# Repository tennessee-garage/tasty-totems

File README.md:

# tasty-totems
Repo for a zoetrope type of art project

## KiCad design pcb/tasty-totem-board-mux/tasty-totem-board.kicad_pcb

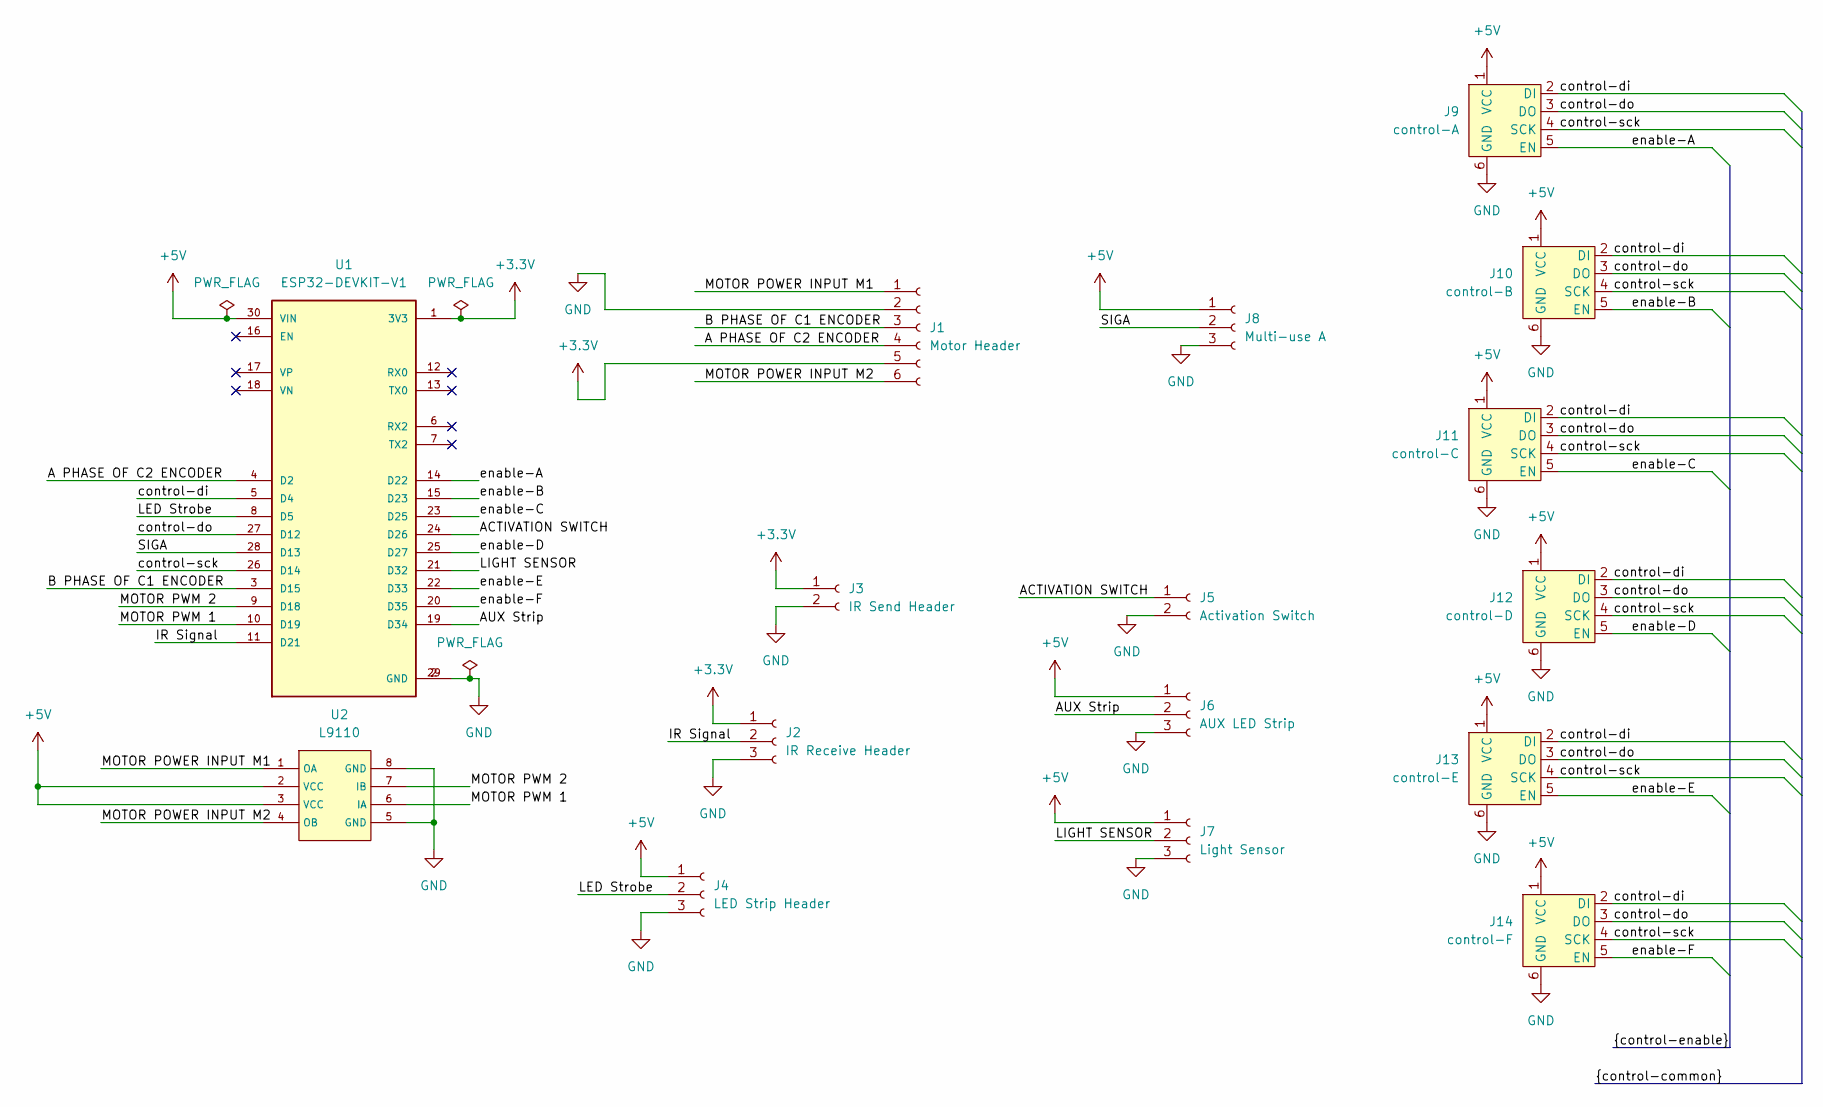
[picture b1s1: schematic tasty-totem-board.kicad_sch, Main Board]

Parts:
J1: Motor Header; PinSocket_1x06_P2.54mm_Horizontal
J2: IR Receive Header; PinSocket_1x03_P2.54mm_Horizontal
J3: IR Send Header; PinSocket_1x02_P2.54mm_Horizontal
J4: LED Strip Header; PinSocket_1x03_P2.54mm_Horizontal
J5: Activation Switch; PinSocket_1x02_P2.54mm_Horizontal
J6: AUX LED Strip; PinSocket_1x03_P2.54mm_Horizontal
J7: Light Sensor; PinSocket_1x03_P2.54mm_Horizontal
J8: Multi-use A; PinSocket_1x03_P2.54mm_Horizontal
J9: control-A; RJ11-RA
J10: control-B; RJ11-RA
J11: control-C; RJ11-RA
J12: control-D; RJ11-RA
J13: control-E; RJ11-RA
J14: control-F; RJ11-RA
U1: ESP32-DEVKIT-V1; MODULE_ESP32_DEVKIT_V1; PARTREV N/A
U2: L9110; DIP-8_W7.62mm

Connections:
+3.3V: J1.5, J2.1, J3.1, U1.1 (3V3)
+5V: J4.1, J6.1, J7.1, J8.1, J9.1 (VCC), J10.1 (VCC), J11.1 (VCC), J12.1 (VCC), J13.1 (VCC), J14.1 (VCC), U1.30 (VIN), U2.2 (VCC), U2.3 (VCC)
/A PHASE OF C2 ENCODER: J1.4, U1.4 (D2)
/ACTIVATION SWITCH: J5.1, U1.24 (D26)
/AUX Strip: J6.2, U1.19 (D34)
/B PHASE OF C1 ENCODER: J1.3, U1.3 (D15)
/IR Signal: J2.2, U1.11 (D21)
/LED Strobe: J4.2, U1.8 (D5)
/LIGHT SENSOR: J7.2, U1.21 (D32)
/MOTOR POWER INPUT M1: J1.1, U2.1 (OA)
/MOTOR POWER INPUT M2: J1.6, U2.4 (OB)
/MOTOR PWM 1: U1.10 (D19), U2.6 (IA)
/MOTOR PWM 2: U1.9 (D18), U2.7 (IB)
/SIGA: J8.2, U1.28 (D13)
/control-di: J9.2 (DI), J10.2 (DI), J11.2 (DI), J12.2 (DI), J13.2 (DI), J14.2 (DI), U1.5 (D4)
/control-do: J9.3 (DO), J10.3 (DO), J11.3 (DO), J12.3 (DO), J13.3 (DO), J14.3 (DO), U1.27 (D12)
/control-sck: J9.4 (SCK), J10.4 (SCK), J11.4 (SCK), J12.4 (SCK), J13.4 (SCK), J14.4 (SCK), U1.26 (D14)
/enable-A: J9.5 (EN), U1.14 (D22)
/enable-B: J10.5 (EN), U1.15 (D23)
/enable-C: J11.5 (EN), U1.23 (D25)
/enable-D: J12.5 (EN), U1.25 (D27)
/enable-E: J13.5 (EN), U1.22 (D33)
/enable-F: J14.5 (EN), U1.20 (D35)
GND: J1.2, J2.3, J3.2, J4.3, J5.2, J6.3, J7.3, J8.3, J9.6 (GND), J10.6 (GND), J11.6 (GND), J12.6 (GND), J13.6 (GND), J14.6 (GND), U1.2 (GND), U1.29 (GND), U2.5 (GND), U2.8 (GND)

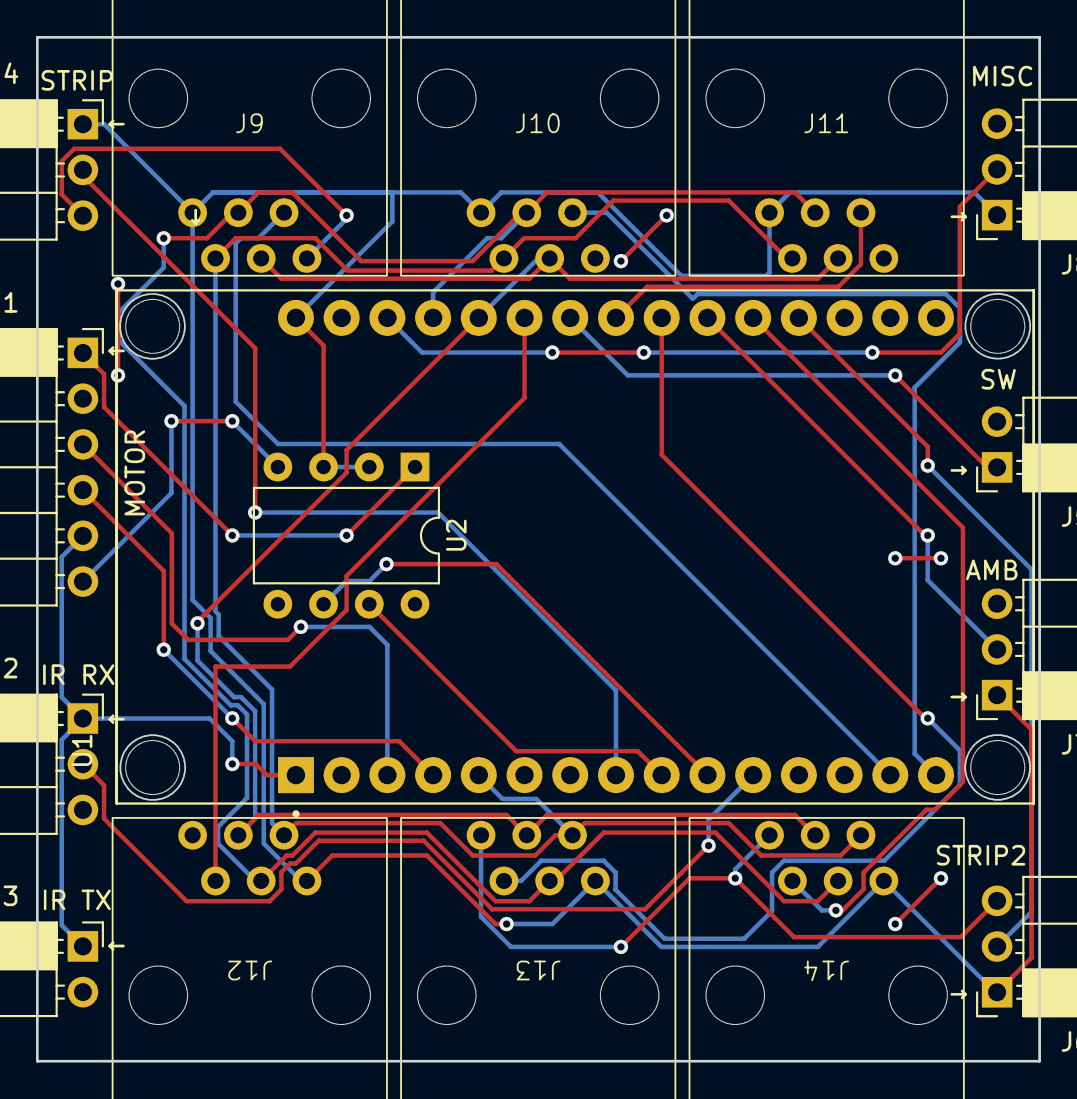
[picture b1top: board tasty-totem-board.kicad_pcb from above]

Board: 2 copper layers, 55.7 x 56.9 mm, 16 parts (0 on the bottom side), 24 nets.

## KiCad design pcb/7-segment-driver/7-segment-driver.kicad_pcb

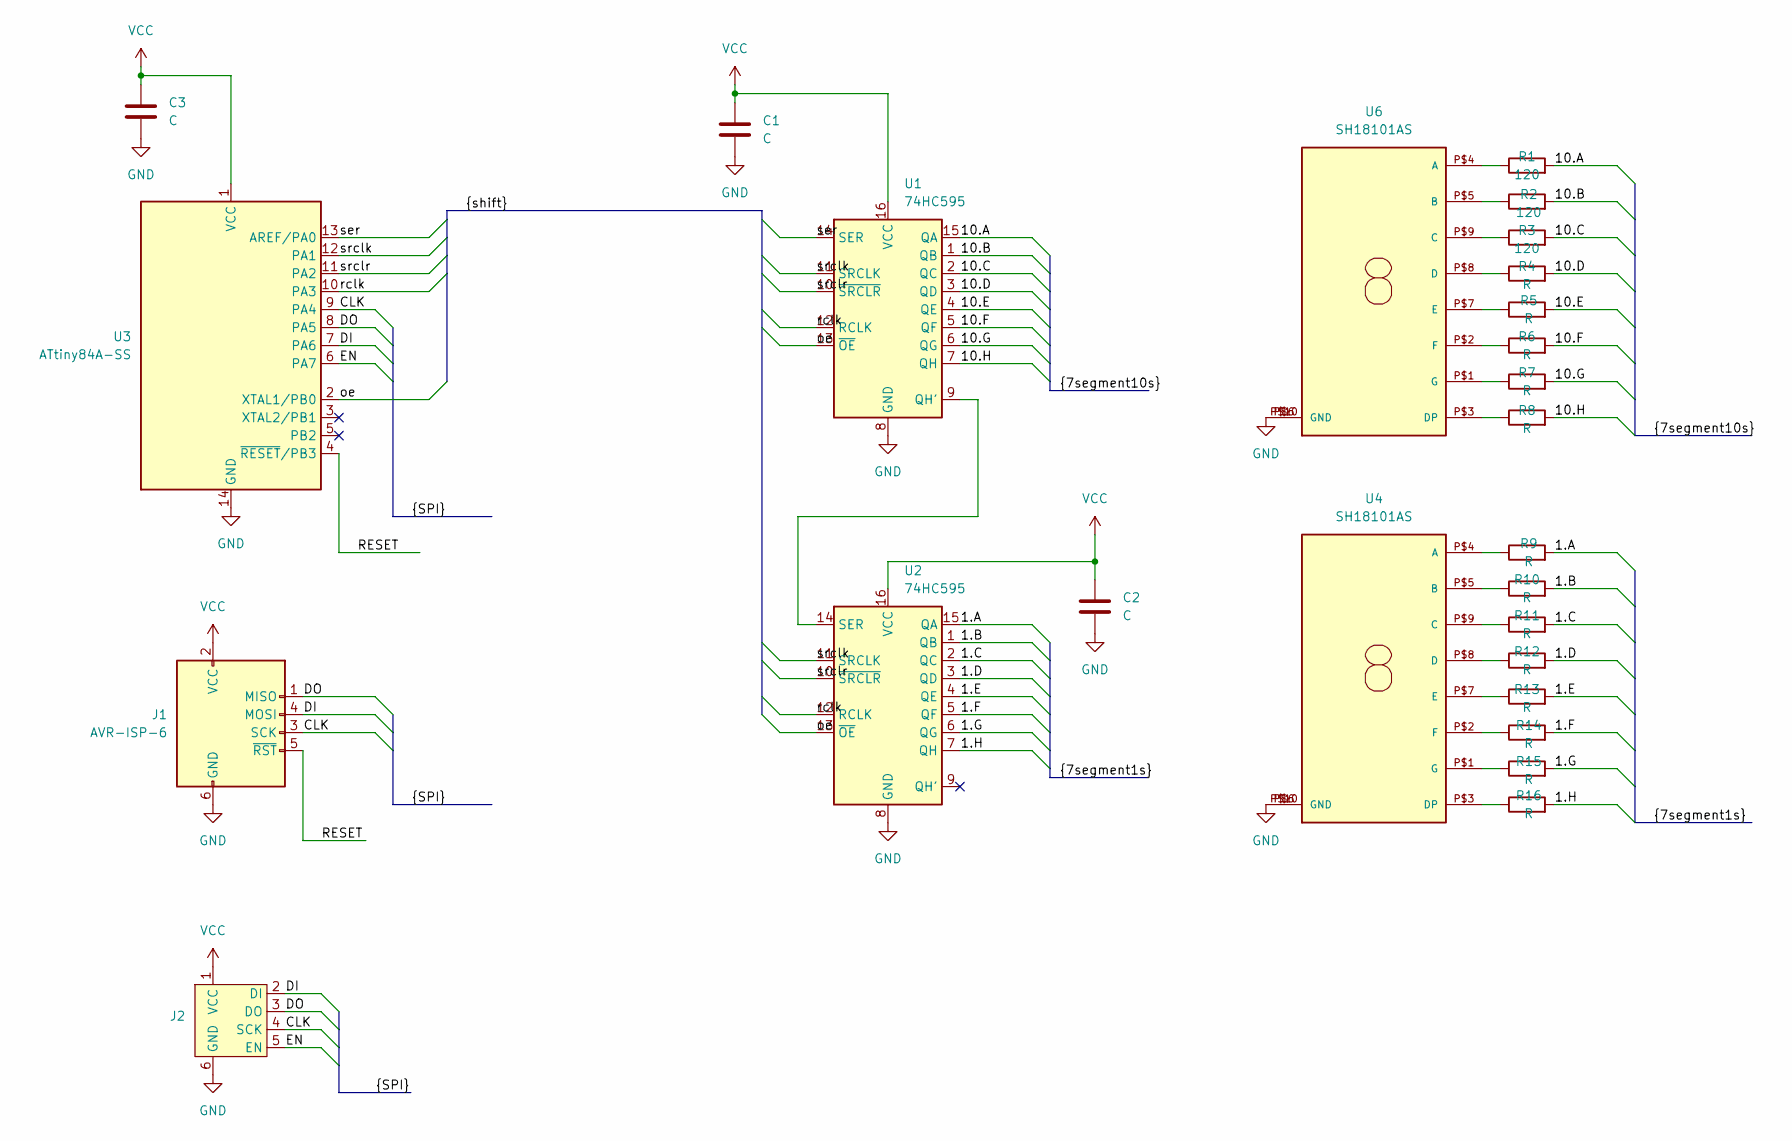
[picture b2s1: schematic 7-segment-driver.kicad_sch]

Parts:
C1, C2, C3: C; C_0805_2012Metric
J1: AVR-ISP-6; IDC-Header_2x03_P2.54mm_Vertical
J2: RJ11-Straight
R1, R2, R3: 120; R_0805_2012Metric_Pad1.20x1.40mm_HandSolder
R4, R5, R6, R7, R8, R9, R10, R11, R12, R13, R14, R15, R16: R; R_0805_2012Metric_Pad1.20x1.40mm_HandSolder
U1, U2: 74HC595; TSSOP-16_4.4x5mm_P0.65mm
U3: ATtiny84A-SS; SOIC-14_3.9x8.7mm_P1.27mm
U4, U6: SH18101AS

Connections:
/1.A: R9.2, U2.15 (QA)
/1.B: R10.2, U2.1 (QB)
/1.C: R11.2, U2.2 (QC)
/1.D: R12.2, U2.3 (QD)
/1.E: R13.2, U2.4 (QE)
/1.F: R14.2, U2.5 (QF)
/1.G: R15.2, U2.6 (QG)
/1.H: R16.2, U2.7 (QH)
/10.A: R1.2, U1.15 (QA)
/10.B: R2.2, U1.1 (QB)
/10.C: R3.2, U1.2 (QC)
/10.D: R4.2, U1.3 (QD)
/10.E: R5.2, U1.4 (QE)
/10.F: R6.2, U1.5 (QF)
/10.G: R7.2, U1.6 (QG)
/10.H: R8.2, U1.7 (QH)
/CLK: J1.3 (SCK), J2.4 (SCK), U3.9 (PA4)
/DI: J1.4 (MOSI), J2.2 (DI), U3.7 (PA6)
/DO: J1.1 (MISO), J2.3 (DO), U3.8 (PA5)
/EN: J2.5 (EN), U3.6 (PA7)
/RESET: J1.5 (~RST), U3.4 (~RESET/PB3)
/oe: U1.13 (~OE), U2.13 (~OE), U3.2 (XTAL1/PB0)
/rclk: U1.12 (RCLK), U2.12 (RCLK), U3.10 (PA3)
/ser: U1.14 (SER), U3.13 (AREF/PA0)
/srclk: U1.11 (SRCLK), U2.11 (SRCLK), U3.12 (PA1)
/srclr: U1.10 (~SRCLR), U2.10 (~SRCLR), U3.11 (PA2)
GND: C1.2, C2.2, C3.2, J1.6 (GND), J2.6 (GND), U1.8 (GND), U2.8 (GND), U3.14 (GND), U4.P$6 (GND), U4.P$10 (GND), U6.P$6 (GND), U6.P$10 (GND)
unnamed: U1.9 (QH'), U2.14 (SER)
unnamed: R9.1, U4.P$4 (A)
unnamed: R10.1, U4.P$5 (B)
unnamed: R11.1, U4.P$9 (C)
unnamed: R12.1, U4.P$8 (D)
unnamed: R16.1, U4.P$3 (DP)
unnamed: R13.1, U4.P$7 (E)
unnamed: R14.1, U4.P$2 (F)
unnamed: R15.1, U4.P$1 (G)
unnamed: R1.1, U6.P$4 (A)
unnamed: R2.1, U6.P$5 (B)
unnamed: R3.1, U6.P$9 (C)
unnamed: R4.1, U6.P$8 (D)
unnamed: R8.1, U6.P$3 (DP)
unnamed: R5.1, U6.P$7 (E)
unnamed: R6.1, U6.P$2 (F)
unnamed: R7.1, U6.P$1 (G)
VCC: C1.1, C2.1, C3.1, J1.2 (VCC), J2.1 (VCC), U1.16 (VCC), U2.16 (VCC), U3.1 (VCC)

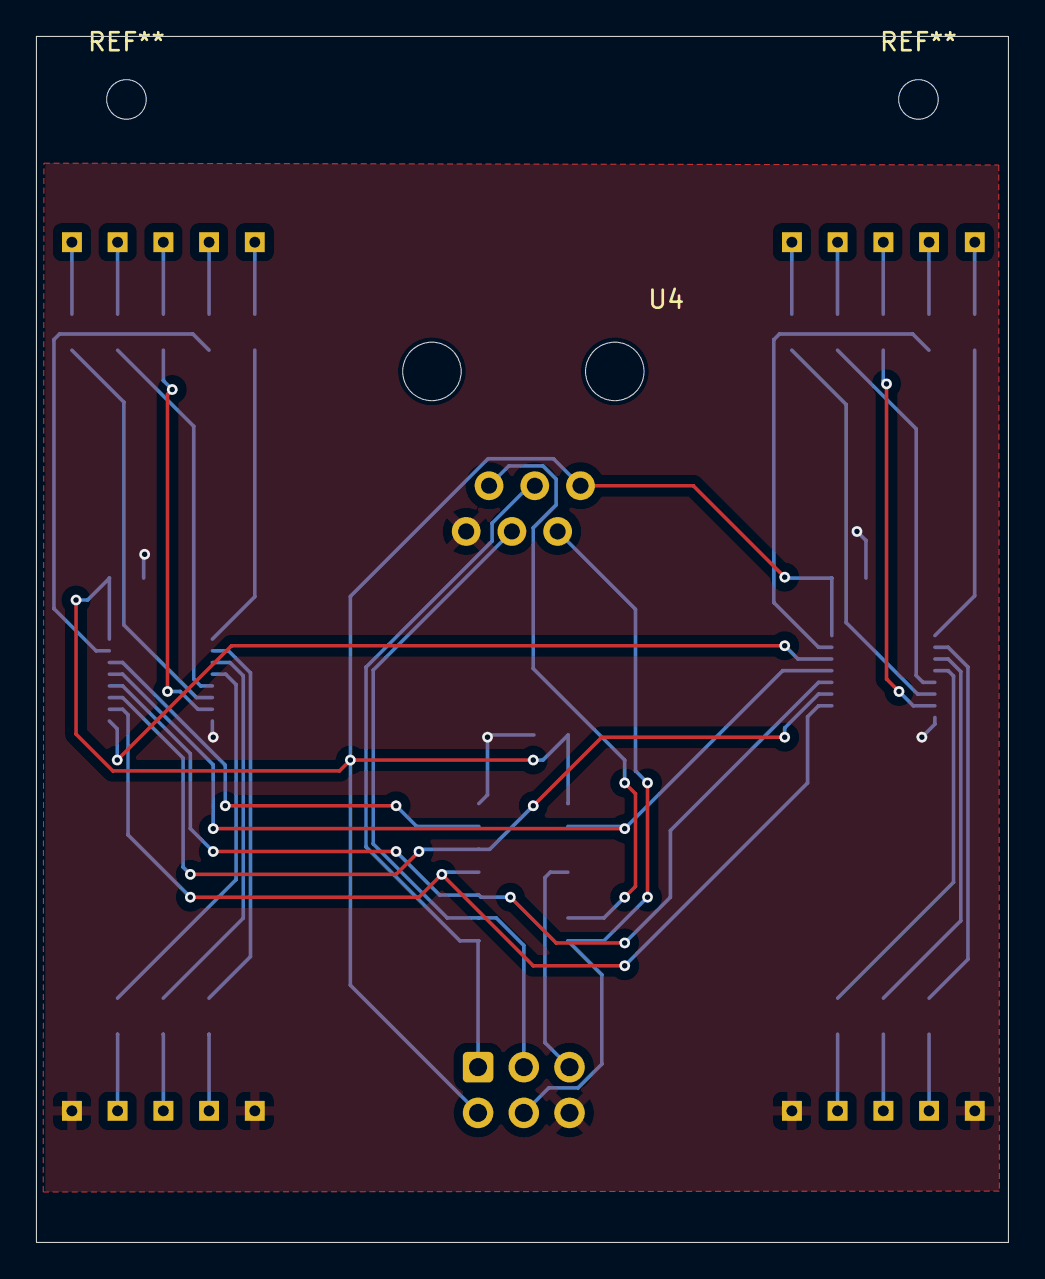
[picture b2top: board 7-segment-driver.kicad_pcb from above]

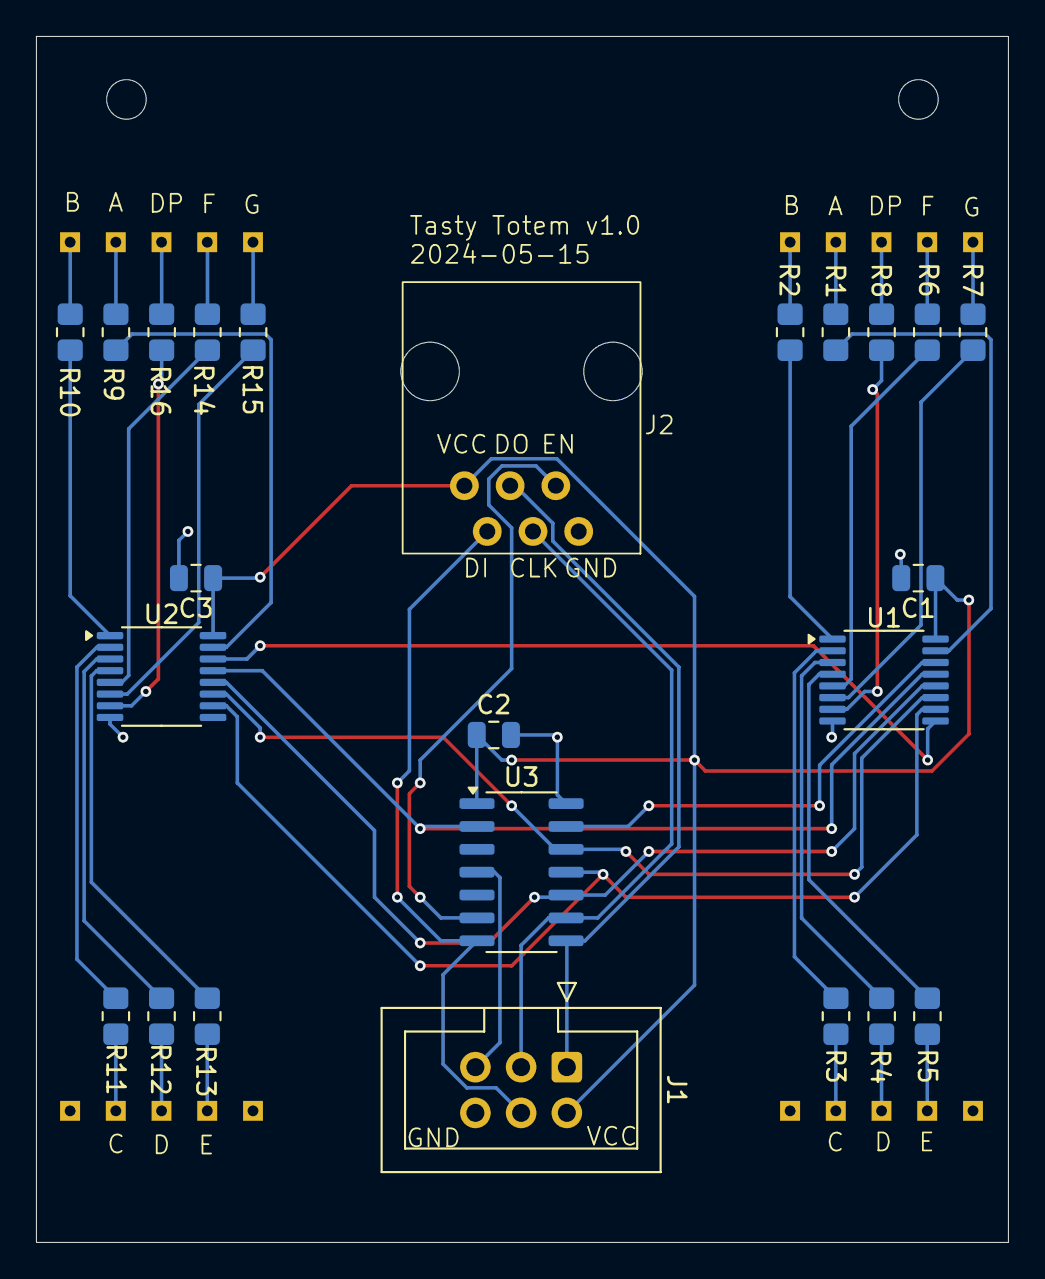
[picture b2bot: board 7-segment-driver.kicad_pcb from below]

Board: 2 copper layers, 54.0 x 67.0 mm, 26 parts (24 on the bottom side), 45 nets.

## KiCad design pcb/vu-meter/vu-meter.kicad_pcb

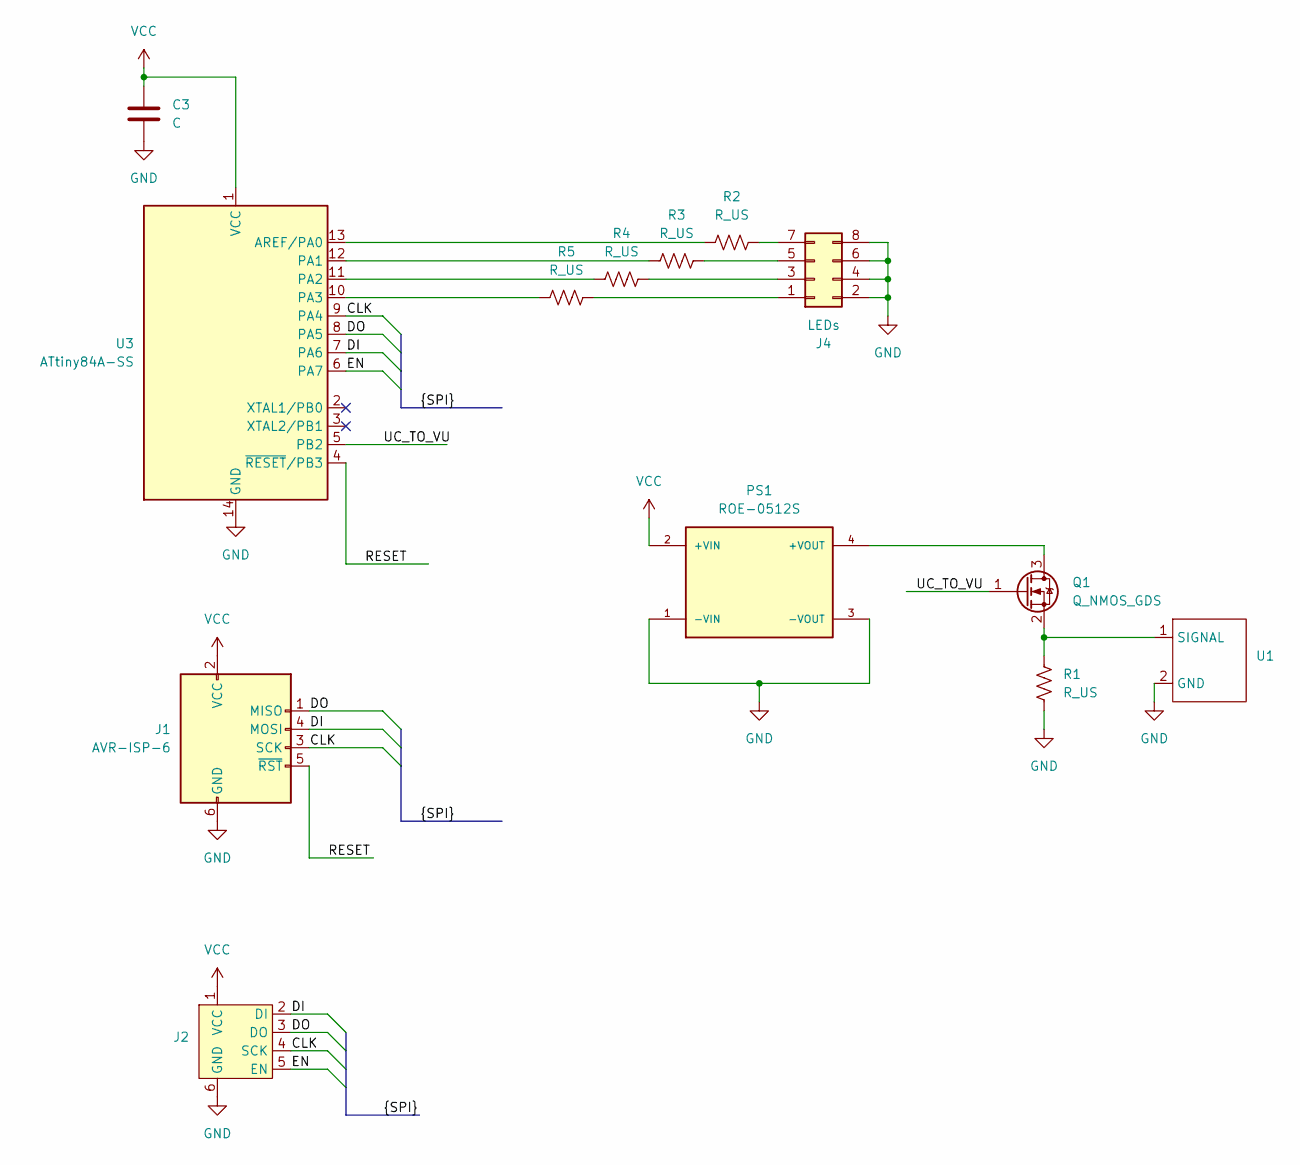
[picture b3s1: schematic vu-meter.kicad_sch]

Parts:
C3: C; C_0805_2012Metric
J1: AVR-ISP-6; IDC-Header_2x03_P2.54mm_Vertical
J2: RJ11-Straight
J4: LEDs; PinHeader_2x04_P2.54mm_Vertical
PS1: ROE-0512S; CONV_ROE-0512S; PARTREV 5
Q1: Q_NMOS_GDS; SOT-323_SC-70_Handsoldering
R1, R2, R3, R4, R5: R_US; R_0805_2012Metric_Pad1.20x1.40mm_HandSolder
U1: VU-Meter
U3: ATtiny84A-SS; SOIC-14_3.9x8.7mm_P1.27mm

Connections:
/CLK: J1.3 (SCK), J2.4 (SCK), U3.9 (PA4)
/DI: J1.4 (MOSI), J2.2 (DI), U3.7 (PA6)
/DO: J1.1 (MISO), J2.3 (DO), U3.8 (PA5)
/EN: J2.5 (EN), U3.6 (PA7)
/RESET: J1.5 (~RST), U3.4 (~RESET/PB3)
/UC_TO_VU: Q1.1 (G), U3.5 (PB2)
GND: C3.2, J1.6 (GND), J2.6 (GND), J4.2, J4.4, J4.6, J4.8, PS1.1 (-VIN), PS1.3 (-VOUT), R1.2, U1.2 (GND), U3.14 (GND)
unnamed: J4.1, R5.2
unnamed: J4.3, R4.2
unnamed: J4.5, R3.2
unnamed: J4.7, R2.2
unnamed: PS1.4 (+VOUT), Q1.3 (D)
unnamed: Q1.2 (S), R1.1, U1.1 (SIGNAL)
unnamed: R2.1, U3.13 (AREF/PA0)
unnamed: R3.1, U3.12 (PA1)
unnamed: R4.1, U3.11 (PA2)
unnamed: R5.1, U3.10 (PA3)
VCC: C3.1, J1.2 (VCC), J2.1 (VCC), PS1.2 (+VIN), U3.1 (VCC)

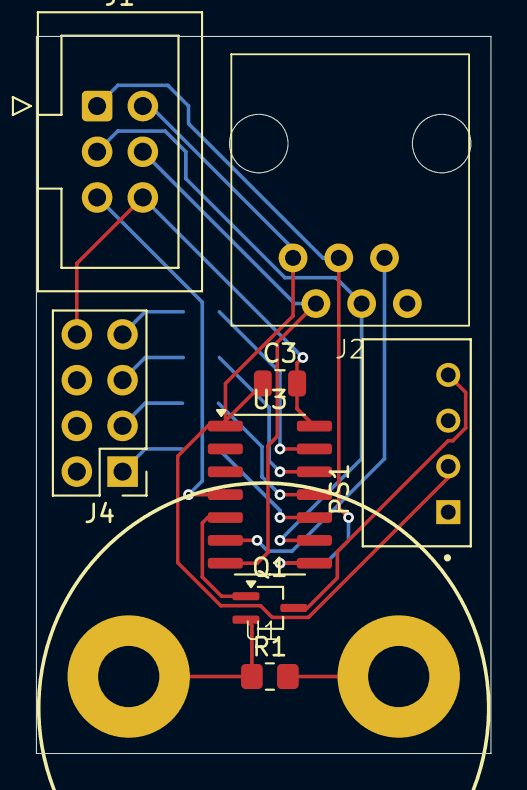
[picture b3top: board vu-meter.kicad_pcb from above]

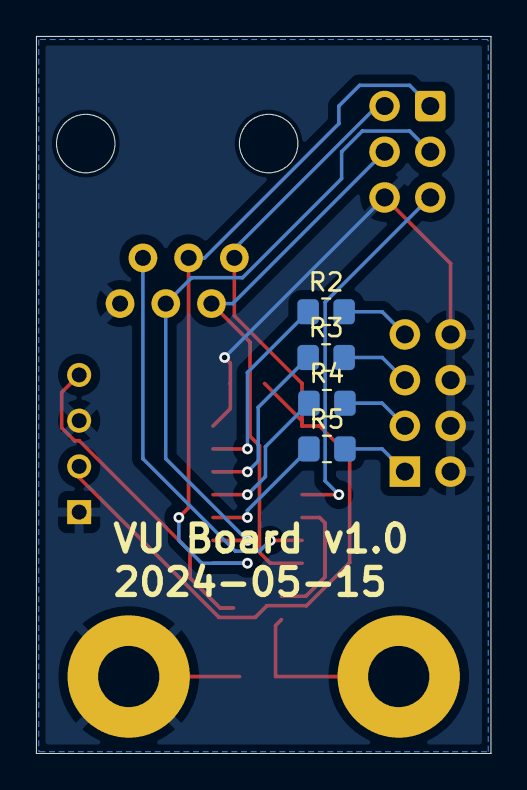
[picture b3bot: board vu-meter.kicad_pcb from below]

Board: 2 copper layers, 25.3 x 39.8 mm, 13 parts (4 on the bottom side), 18 nets.

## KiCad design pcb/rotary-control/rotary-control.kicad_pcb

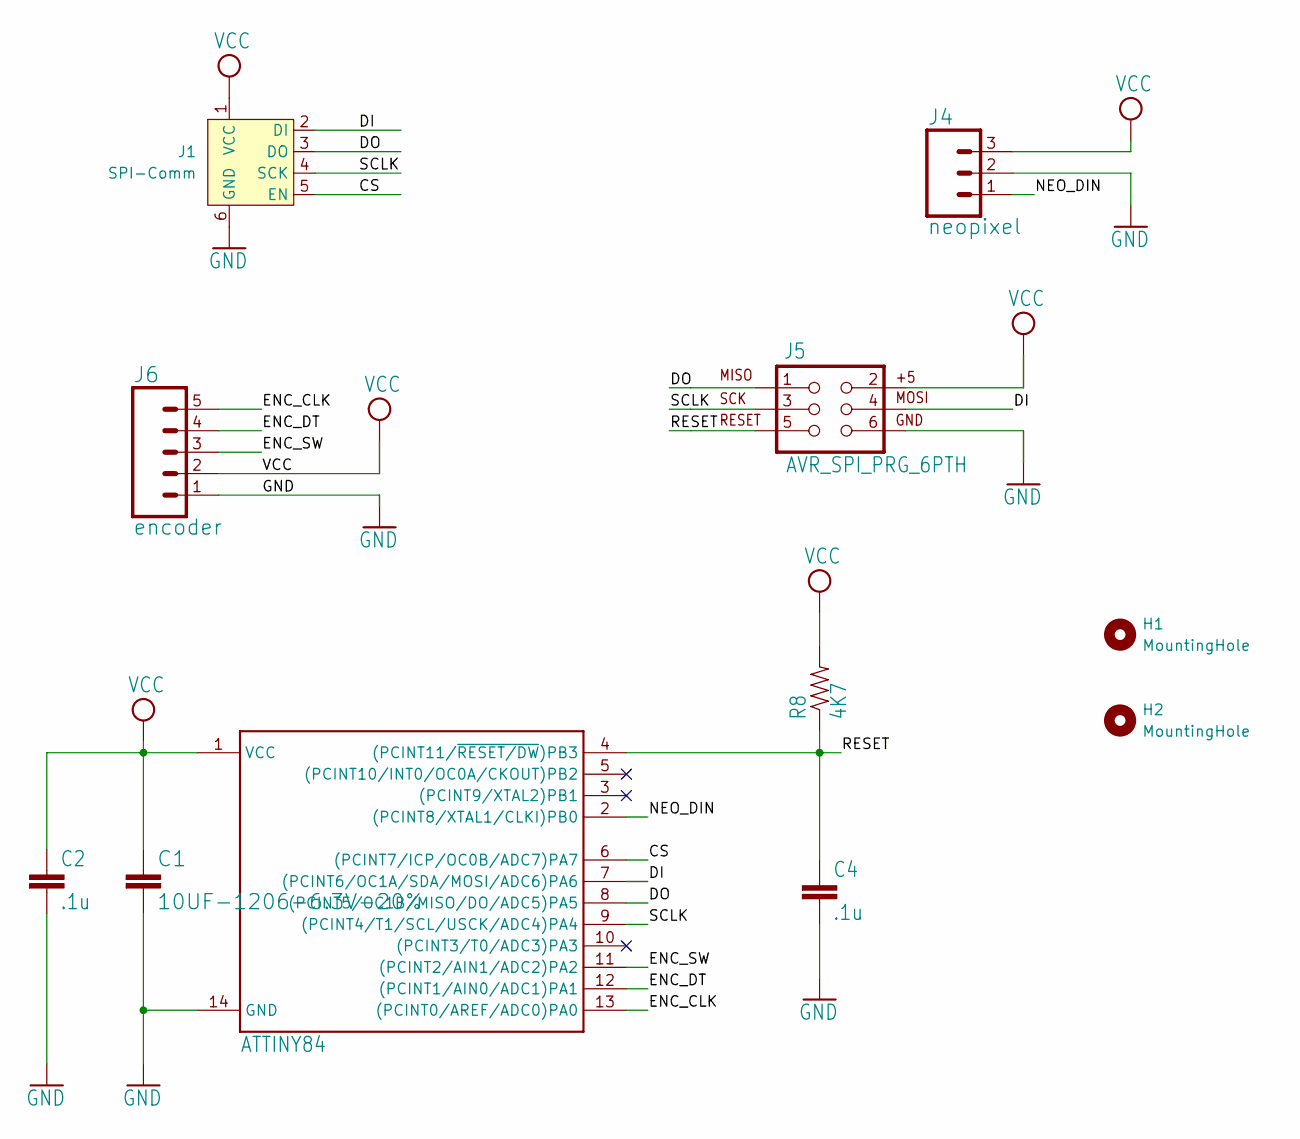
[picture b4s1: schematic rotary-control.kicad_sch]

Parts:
C1: 10UF-1206-6.3V-20%; C_1206_3216Metric_Pad1.33x1.80mm_HandSolder
C2, C4: .1u; 0805
H1, H2: MountingHole; MountingHole_2.7mm_M2.5_Pad
J1: SPI-Comm; RJ11-Straight
J4: neopixel; PinHeader_1x03_P2.54mm_Vertical
J5: AVR_SPI_PRG_6PTH; 2X3
J6: encoder; PinHeader_1x05_P2.54mm_Vertical
R8: 4K7; 0805
U$2: ATTINY84; SOIC-14_3.9x8.7mm_P1.27mm

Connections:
/CS: J1.5 (EN), U$2.6 ((PCINT7/ICP/OC0B/ADC7)PA7)
/DI: J1.2 (DI), J5.4, U$2.7 ((PCINT6/OC1A/SDA/MOSI/ADC6)PA6)
/DO: J1.3 (DO), J5.1, U$2.8 ((PCINT5/OC1B/MISO/DO/ADC5)PA5)
/ENC_CLK: J6.5, U$2.13 ((PCINT0/AREF/ADC0)PA0)
/ENC_DT: J6.4, U$2.12 ((PCINT1/AIN0/ADC1)PA1)
/ENC_SW: J6.3, U$2.11 ((PCINT2/AIN1/ADC2)PA2)
/NEO_DIN: J4.1, U$2.2 ((PCINT8/XTAL1/CLKI)PB0)
/RESET: C4.1, J5.5, R8.1, U$2.4 ((PCINT11/~RESET/DW)PB3)
/SCLK: J1.4 (SCK), J5.3, U$2.9 ((PCINT4/T1/SCL/USCK/ADC4)PA4)
GND: C1.2, C2.2, C4.2, J1.6 (GND), J4.2, J5.6, J6.1, U$2.14 (GND)
VCC: C1.1, C2.1, J1.1 (VCC), J4.3, J5.2, J6.2, R8.2, U$2.1 (VCC)

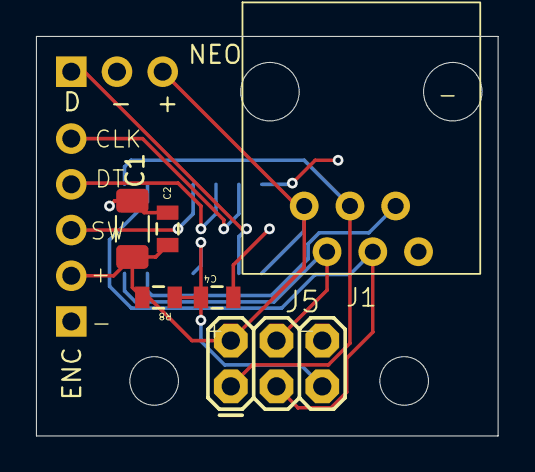
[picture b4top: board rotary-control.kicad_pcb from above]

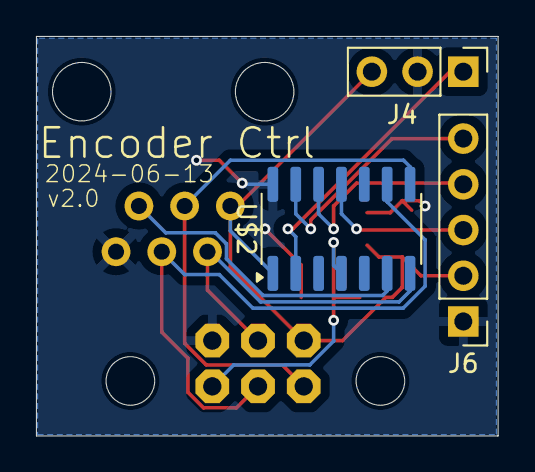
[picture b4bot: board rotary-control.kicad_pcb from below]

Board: 2 copper layers, 25.6 x 22.2 mm, 11 parts (3 on the bottom side), 11 nets.

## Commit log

2023-06-18 First working version of software
2023-07-16 Uploaded new version of driver code, art and pcb files
    Driver code now broken out into classes.
    PCB files are incomplete but bookmarking here to get the new structure in git
2024-04-11 Add in the code as a vcode project
2024-04-11 Remove the CLion project code
2024-04-13 Separate out code to a greater extent
    * Move relavent constants out to specific handler classes
    * Create an encoder class
    * Create a rotation (IR) handler class
    * New main header for constants, to help sharing with other test files
    * Reduce the amount of code in the main tasty-totems.cpp
2024-04-13 Adding a new experiment file, plus an environment to build it
2024-04-13 Add ability to change the pwm frequency via analog input
2024-04-13 Start for candle animation on drum
2024-04-13 Generated gerber files
2024-04-13 Checkpoint current version of PCB design files
2024-04-17 Got PID controller to a working state with reasonable constants
2024-04-17 New PID control class to encapsulate the PID logic.
    Intention is to pull existing PID code out of the MotorControl class
2024-04-17 Updated all classes/code to use new PID Contoller
    Also
    * flipped motor pins to make clockwise the default direction
    * moved PID constants out to main class
    * shifted around some constants to more appropriate places
2024-04-25 Several changes that make this current iteration a good v1.0. These include * tuning the PID a bit * adding a DrumMonitor class to manage the frames, rotations and other details about the animations 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
2024-05-22 Comitting all prior updates to the board before wiring in SPI ports
2024-05-24 Check in imoprted (from eagle) rotary-control
2024-05-24 An ignore file for kicad stuff
2024-05-24 Checkin boards that have been designed and already sent out
2024-07-24 Remove this copied library
    Instead, rely on VS Code to manage dependencies via platformio.ini
2024-07-24 Checkpoint PCB files.
